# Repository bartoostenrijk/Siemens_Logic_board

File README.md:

# Siemens_Logic_board
Here I share the PCB files with which to replace an existing SIEMENS SIMOTION logic board, as used in the Think City car

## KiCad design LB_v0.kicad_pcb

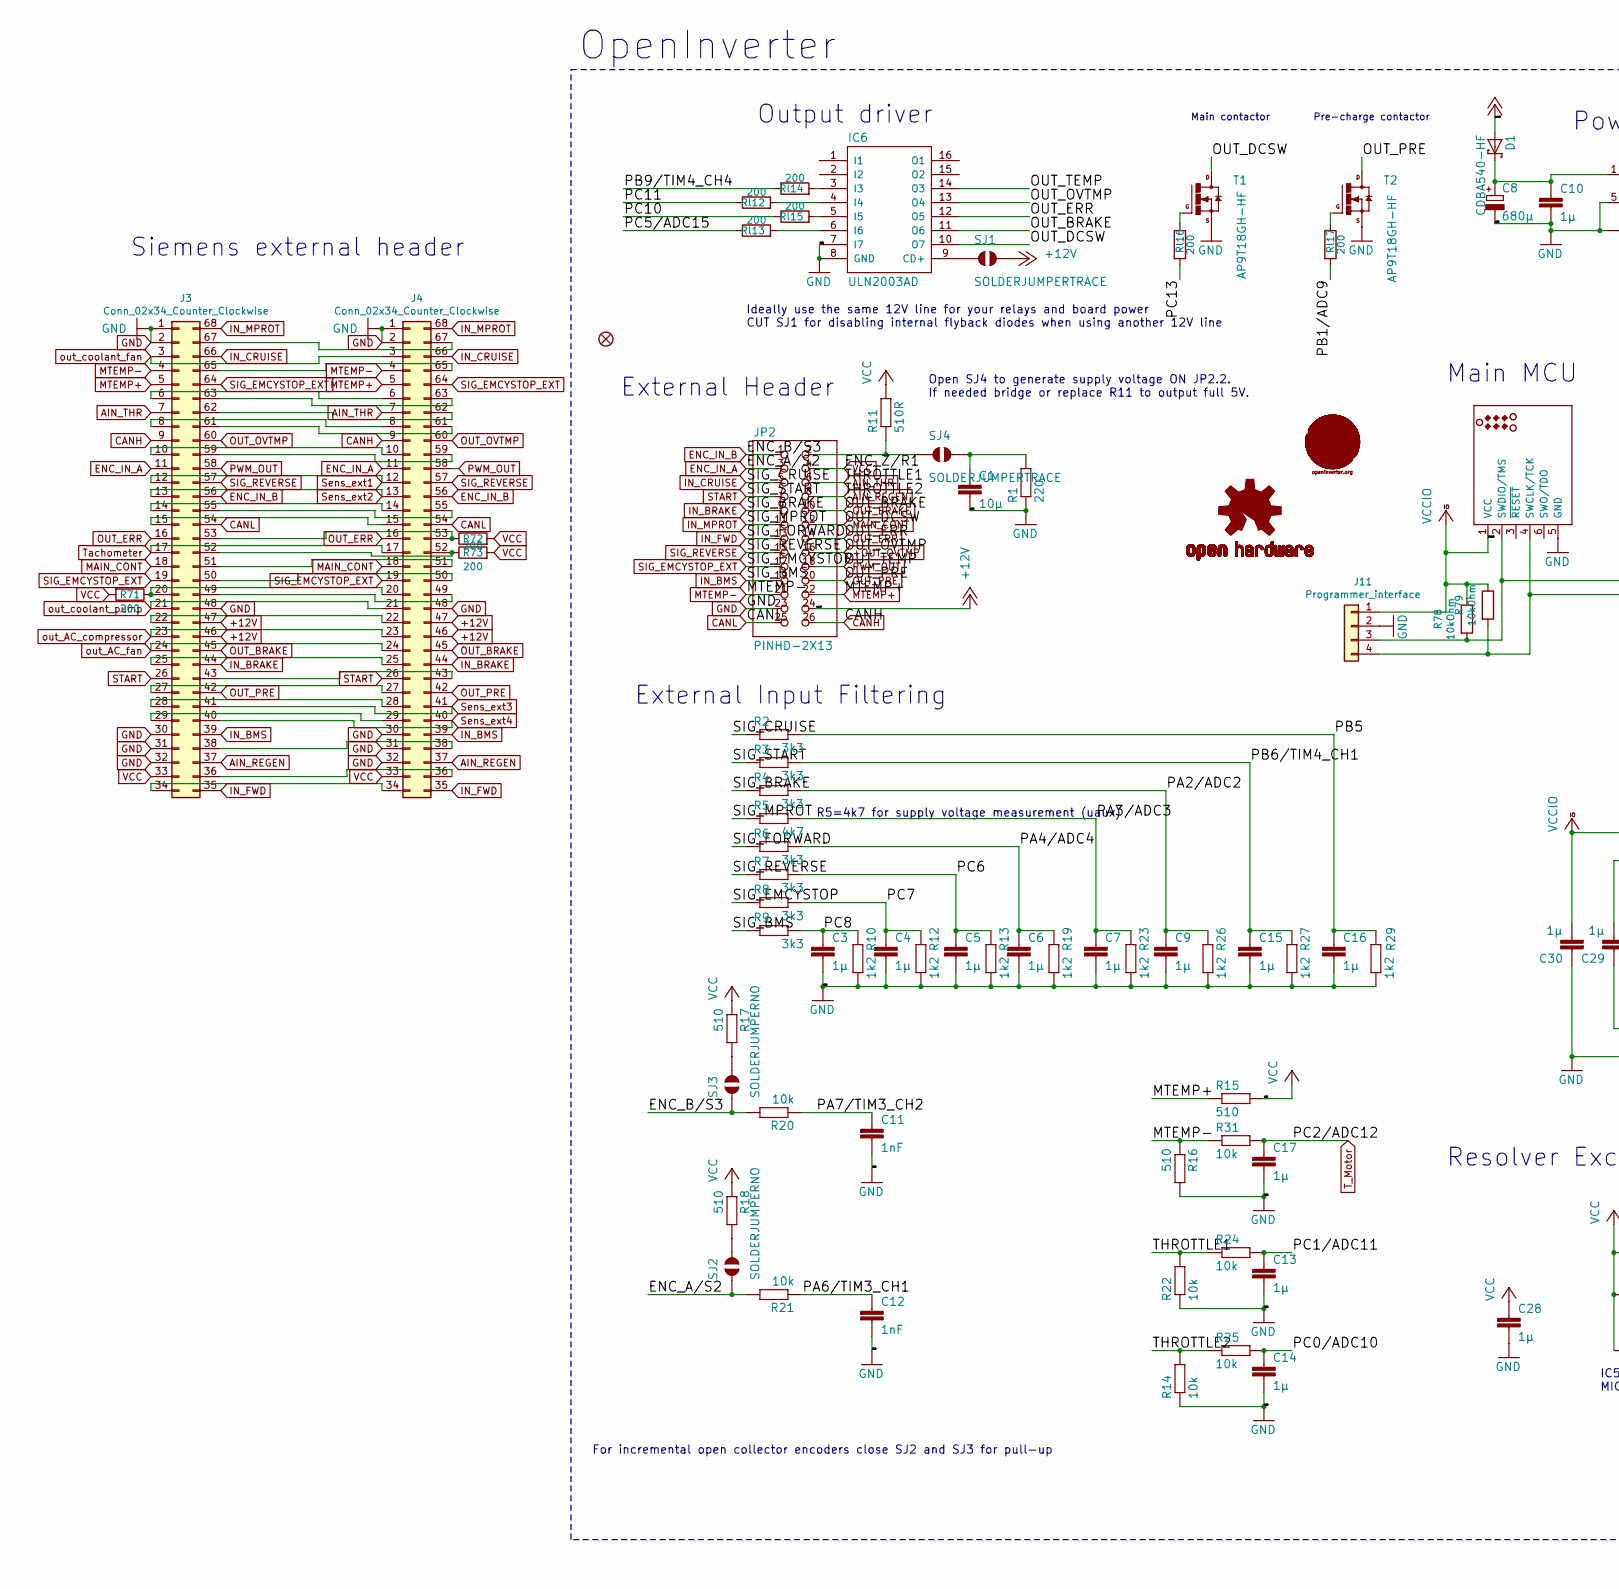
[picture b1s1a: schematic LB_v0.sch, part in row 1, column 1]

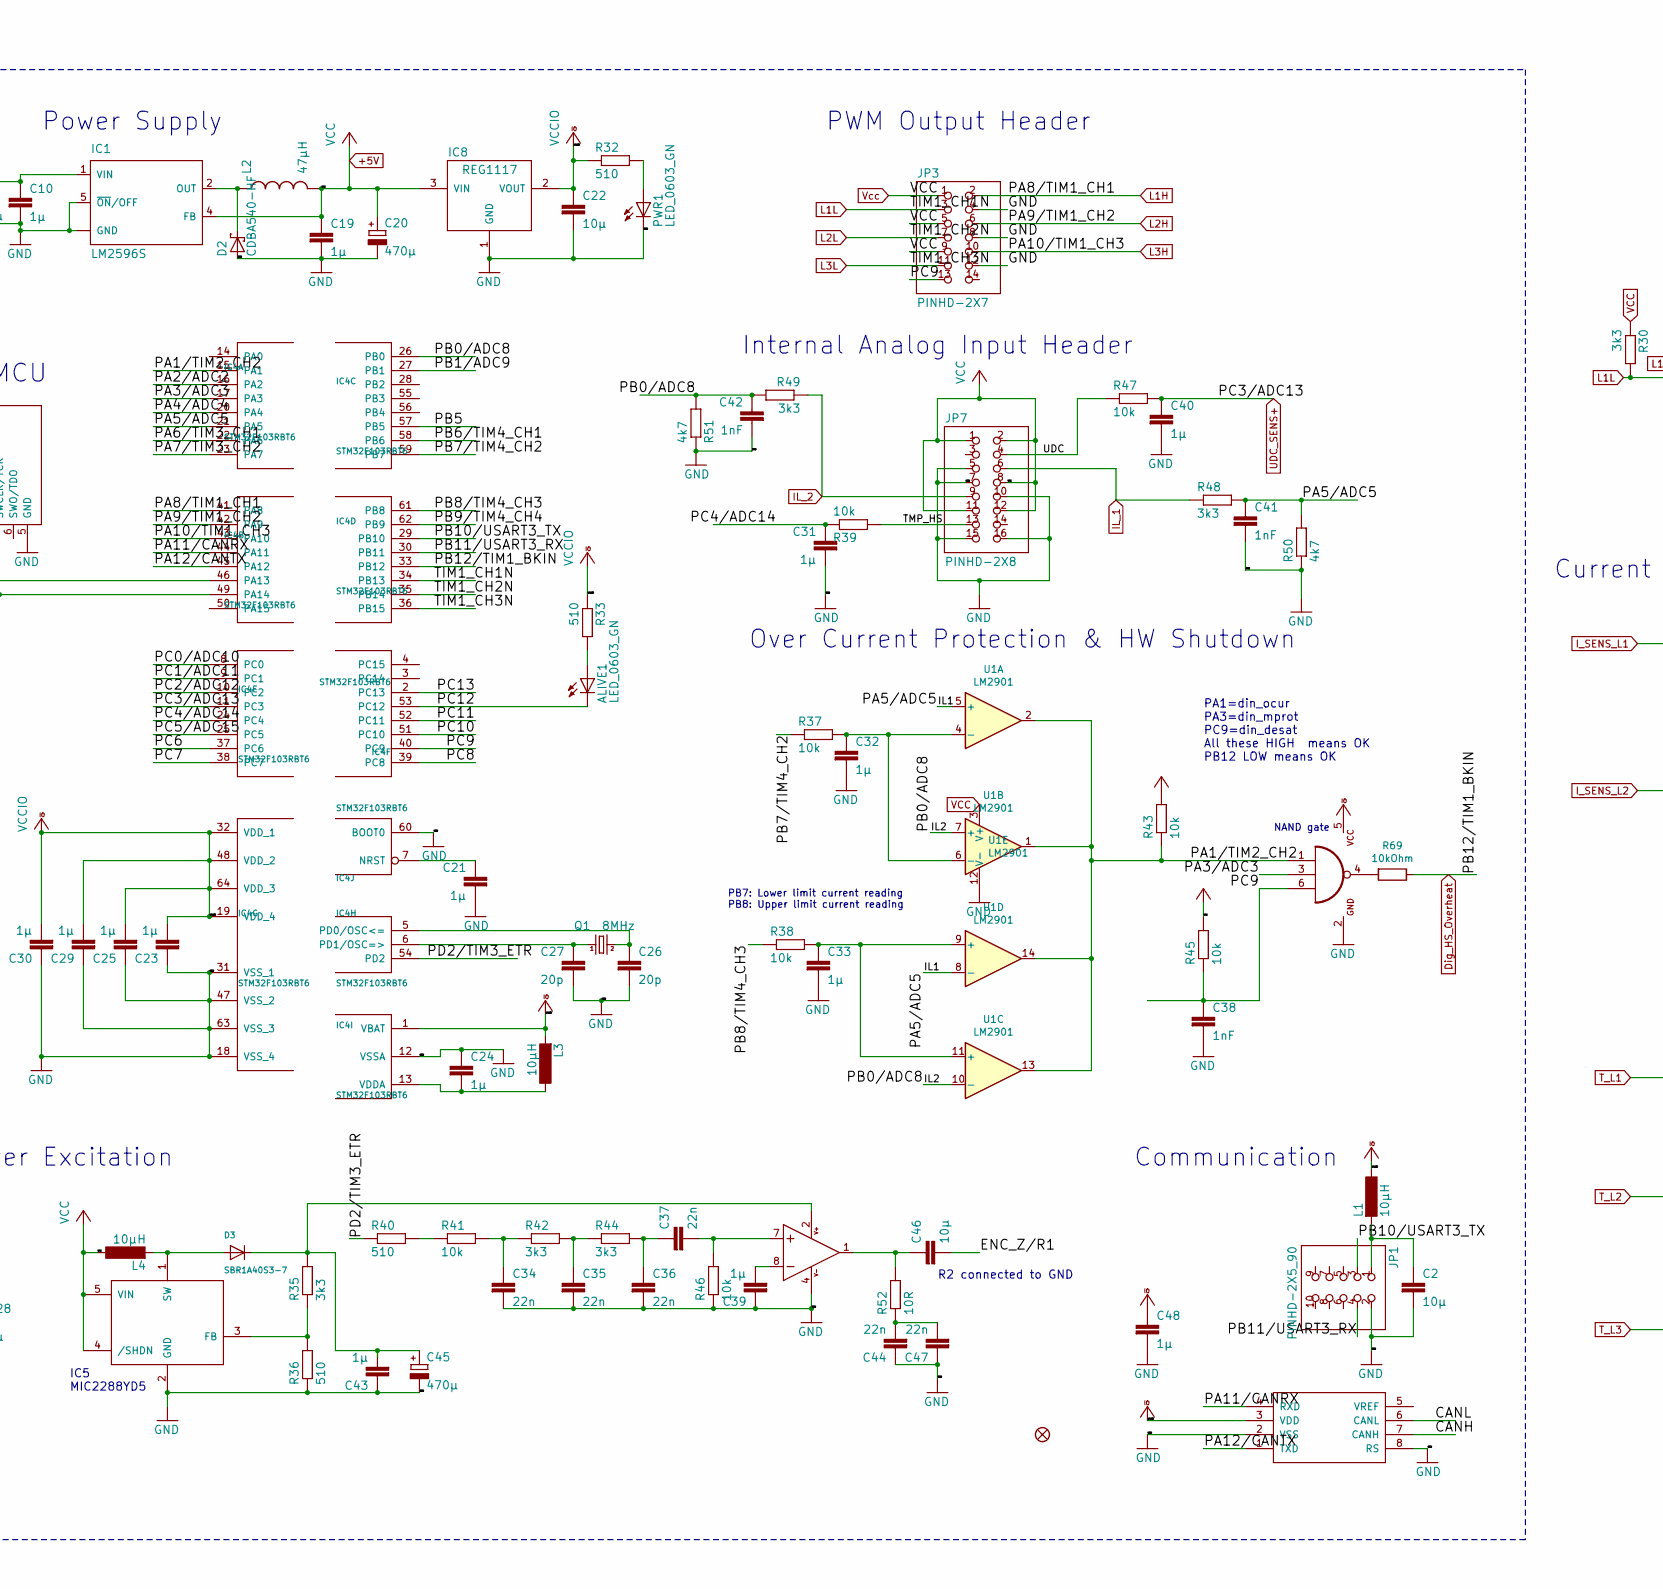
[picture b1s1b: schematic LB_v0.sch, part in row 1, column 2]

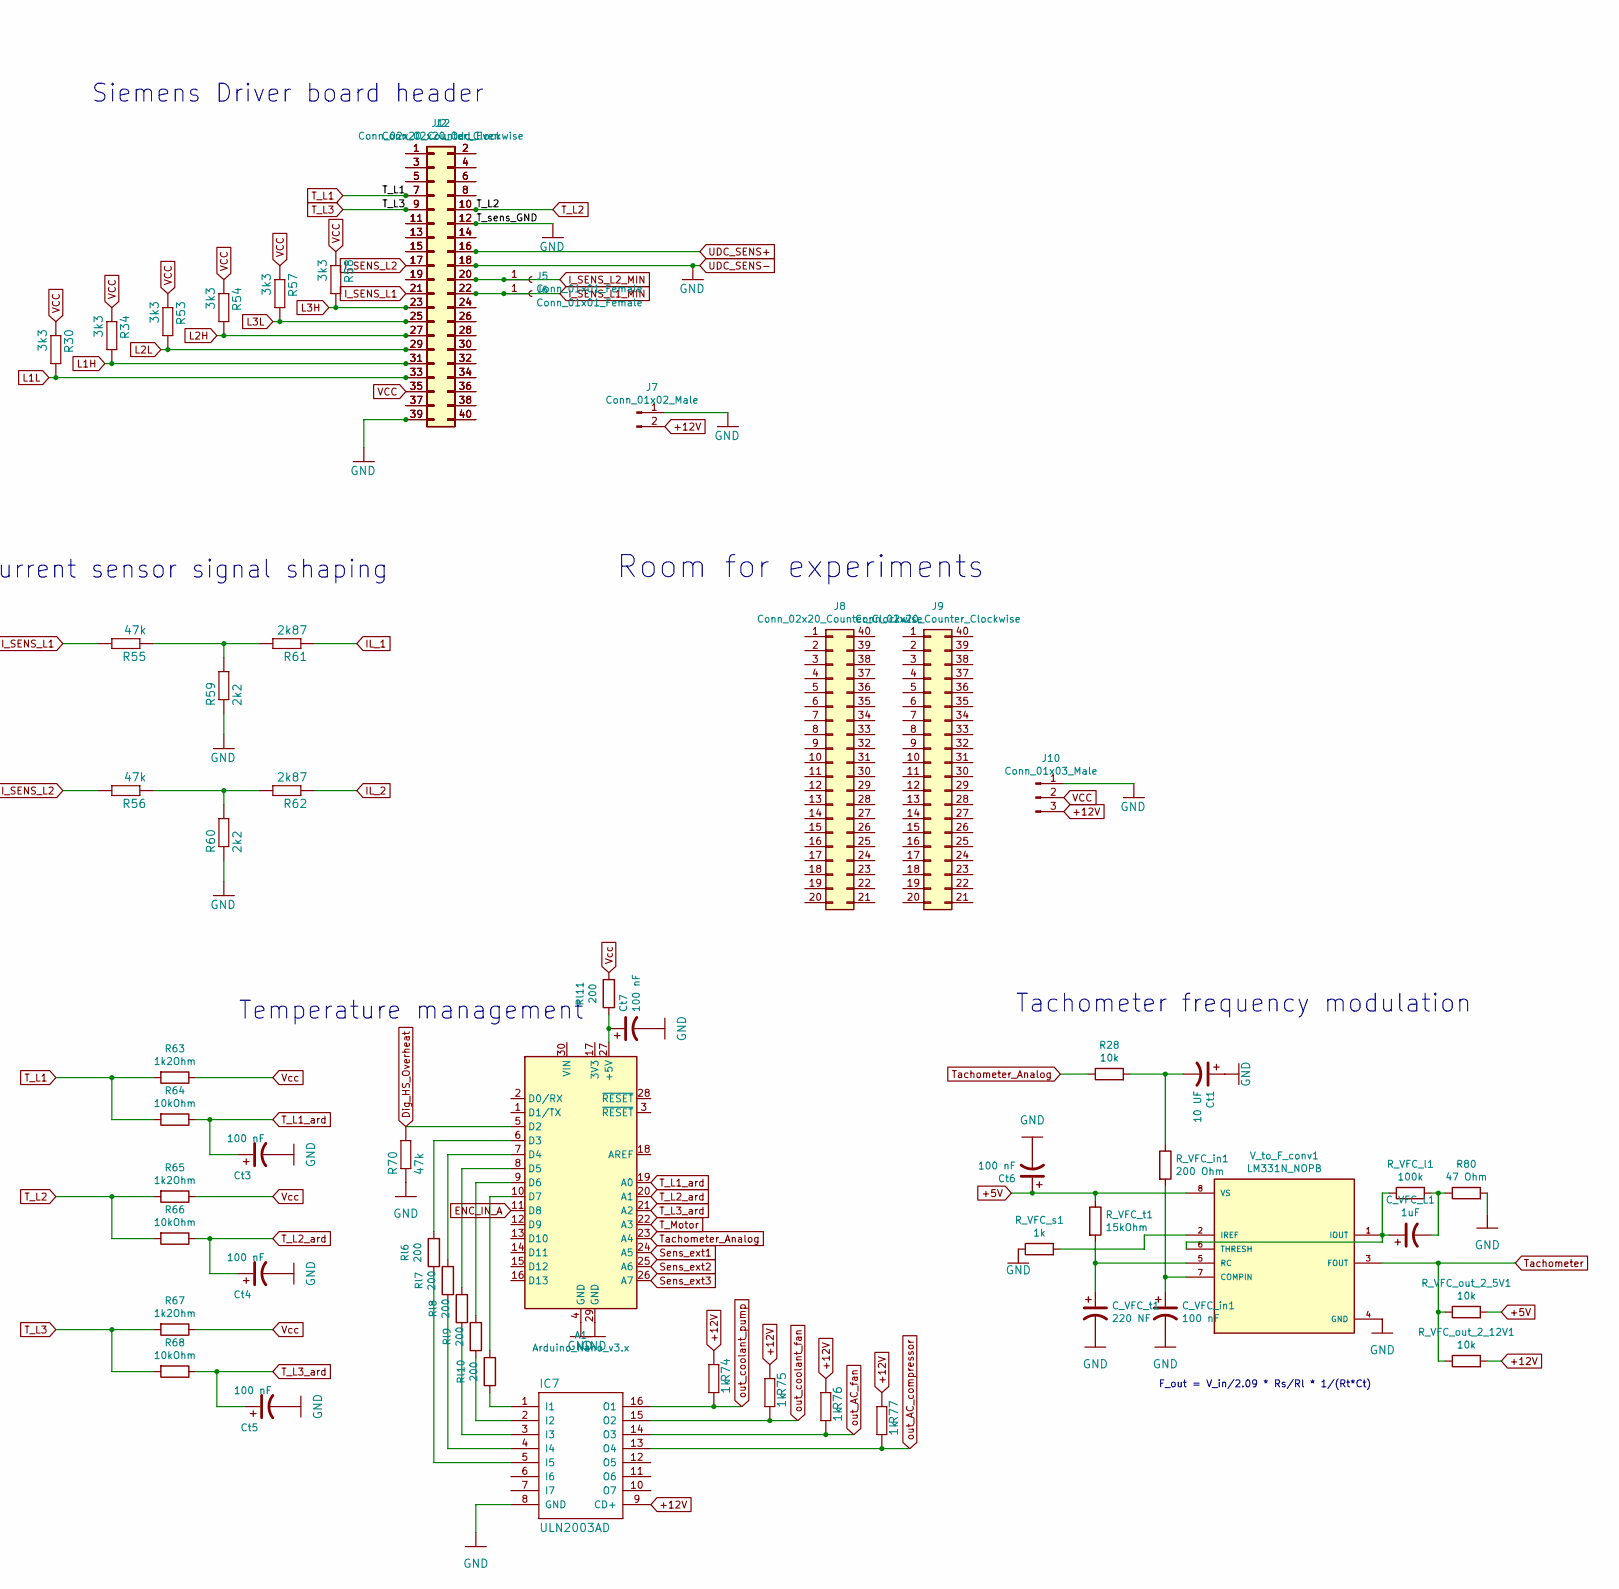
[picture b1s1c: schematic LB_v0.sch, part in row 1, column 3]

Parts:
A1: Arduino_Nano_v3.x; Arduino_Nano
ALIVE1: LED_0603_GN; SML0805; LCSC C84256
C1, C2, C22, C46: 10µ; C0805; LCSC C15850
C3, C4, C5, C6, C7, C9, C10, C13, C14, C15, C16, C17, C19, C21, C23, C24, C25, C28, C29, C30, C31, C32, C33, C39, C40, C43, C48: 1µ; C0603; LCSC C28323
C8: 680µ; UD-10X10_NICHICON; LCSC C249931
C11, C12, C38, C41, C42: 1nF; C0603; LCSC C46653
C20: 470µ; UD-6,3X7,7_NICHICON; LCSC C134738
C26, C27: 20p; C0603; LCSC C1804
C34, C35, C36, C37, C44, C47: 22n; C0603; LCSC C21122
C45: 470µ; UD-6,3X7,7_NICHICON; LCSC C134823
C_VFC_L1: 1uF; C_0805_2012Metric; LCSC C28323
C_VFC_in1: 100 nF; C_0603_1608Metric; LCSC C14663
C_VFC_t1: 220 NF; C_0603_1608Metric; LCSC C21120
Ct1: 10 UF; C_0805_2012Metric; LCSC C15850
Ct3, Ct4, Ct5, Ct6, Ct7: 100 nF; C_0603_1608Metric; LCSC C14663
D1, D2: CDBA540-HF; SMB; LCSC C22452
D3: SBR1A40S3-7; SOD-323F; LCSC C2128
FID1, FID2: FIDUCIAL1X2.5; FIDUCIAL-1X2.5
IC1: LM2596S; TO263-5; LCSC C10002
IC2: TDA2822D; SO08; LCSC C73296
IC3: SN65HVD230DR; SOP-8_3.9x4.9mm_P1.27mm; LCSC C258149
IC4: STM32F103RBT6; TQFP64; LCSC C46034
IC5: MIC2288YD5; SOT23-5L; LCSC C7722
IC6, IC7: ULN2003AD; SO16; LCSC C7512
IC8: REG1117; SOT223; LCSC C347229
IC9: NC7SZ10P6X; SC70-6; LCSC C258149
J1: TC2030_SWD-MCP; TC2030-MCP
J2: Conn_02x20_Odd_Even; PinHeader_2x20_P1.27mm_Vertical_SMD
J3, J4: Conn_02x34_Counter_Clockwise; TE_connector_Siemens
J5, J6: Conn_01x01_Female; SolderWirePad_1x01_Drill1mm
J7: Conn_01x02_Male; SolderWirePad_1x02_P7.62mm_Drill2mm
J8, J9, J12: Conn_02x20_Counter_Clockwise; PinHeader_2x20_P2.54mm_Vertical
J10: Conn_01x03_Male; PinHeader_1x03_P2.54mm_Vertical
J11: Programmer_interface; PinHeader_1x04_P2.54mm_Vertical
JP1: PINHD-2X5_90; 2X05_90
JP2: PINHD-2X13; 2X13
JP3: PINHD-2X7; 2X07
JP7: PINHD-2X8; 2X08
L1, L3: 10µH; L2012C; LCSC C1046
L2: 47µH; CDRH125; LCSC C167265
L4: 10µH; L2825P; LCSC C86069
LOGO1: OSHW-LOGOM; OSHW-LOGO-M
PWR1: LED_0603_GN; SML0805; LCSC C84256
Q1: 8MHz; CRYSTAL-TXC-7A; LCSC C115962
R1: 220; R0603; LCSC C22962
R2, R3, R4, R6, R7, R8, R9, R35, R42, R44, R48, R49: 3k3; R0603; LCSC C26010
R5, R50, R51: 4k7; R0603; LCSC C17673
R10, R12, R13, R19, R23, R26, R27, R29: 1k2; R0603; LCSC C22765
R11: 510R; R0603; LCSC C23193
R14, R20, R21, R22, R24, R25, R31, R37, R38, R39, R41, R43, R46, R47: 10k; R0603; LCSC C17414
R15, R16, R32, R33, R36, R40: 510; R0603; LCSC C23193
R17, R18: 510; R0603
R28: 10k; R_Axial_DIN0207_L6.3mm_D2.5mm_P7.62mm_Horizontal
R30, R34, R53, R54, R57, R58: 3k3; R0603; LCSC C25890
R45: 10k; R_1206_3216Metric; LCSC C17902
R52: 10R; R0603; LCSC C22859
R55, R56, R70: 47k; R_0805_2012Metric; LCSC C17713
R59, R60: 2k2; R_0805_2012Metric; LCSC C17520
R61, R62: 2k87; R_0805_2012Metric; LCSC C17533
R63, R65, R67: 1k2Ohm; R_0603_1608Metric; LCSC C22765
R64, R66, R68, R69, R78, R79: 10kOhm; R_1206_3216Metric; LCSC C17902
R71, R72, R73: 200; R_0402_1005Metric; LCSC C25087
R74, R75, R76, R77: 1k; R_0805_2012Metric; LCSC C17513
R80: 47 Ohm; R_0805_2012Metric; LCSC C17714
R_VFC_in1: 200 Ohm; R_0402_1005Metric; LCSC C25087
R_VFC_l1: 100k; R_Axial_DIN0204_L3.6mm_D1.6mm_P5.08mm_Horizontal
R_VFC_out_2_5V1, R_VFC_out_2_12V1: 10k; R_Axial_DIN0207_L6.3mm_D2.5mm_P7.62mm_Horizontal
R_VFC_s1: 1k; R_0603_1608Metric; LCSC C21190
R_VFC_t1: 15kOhm; R_0402_1005Metric; LCSC C25756
Rl6, Rl7, Rl8, Rl9, Rl10, Rl11, Rl12, Rl13, Rl14, Rl15, Rl16, Rl17: 200; R_0402_1005Metric; LCSC C25087
SJ1, SJ4: SOLDERJUMPERTRACE; SJ_2S-TRACE
SJ2, SJ3: SOLDERJUMPERNO; SJ_2S-NO
T1, T2: AP9T18GH-HF; D-PAK_TO252AA; LCSC C124546
U1: LM2901; SOIC-14_3.9x8.7mm_P1.27mm; LCSC C14296
U$1: OI-LOGO; OI_LOGO
V_to_F_conv1: LM331N_NOPB; DIP-8_W7.62mm; PARTREV 4040082/E 04/2010

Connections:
+5V: C19.1, C20.+, C28.1, C46.2, Ct6.1, IC1.4 (FB), IC5.4 (/SHDN), IC5.5 (VIN), IC8.3 (VIN), J2.35, J3.33, J4.33, J10.2, J12.35, JP2.4, JP3.1, JP3.5, JP3.9, JP7.1, JP7.2, JP7.8, JP7.11, JP7.12, L2.2, L4.1, R11.2, R15.2, R17.1, R18.1, R30.1, R34.1, R43.2, R45.2, R53.1, R54.1, R57.1, R58.1, R63.1, R65.1, R67.1, R71.2, R72.2, R73.2, R_VFC_out_2_5V1.2, R_VFC_t1.1, Rl11.2, U1.3 (V+), V_to_F_conv1.8 (VS)
+12V: D1.A, IC7.9 (CD+), J3.46, J3.47, J4.46, J4.47, J7.2, J10.3, JP2.24, R74.1, R75.1, R76.1, R77.1, R_VFC_out_2_12V1.2, SJ1.2
+OUT_OVTMP: IC6.13 (O4), J3.60, J4.60, JP2.16
/IL1: C41.1, IC4.21 (PA5), R48.2, R50.2, U1.5 (+), U1.8 (-)
/IL2: C42.1, IC4.26 (PB0), R49.2, R51.2, U1.7 (+), U1.10 (-)
/PA1/TIM2_CH2: IC4.15 (PA1), IC9.1 (I0), R43.1, U1.1, U1.2, U1.13, U1.14
/PA2/ADC2: C9.1, IC4.16 (PA2), R4.2, R26.2
/PA3/ADC3: C7.1, IC4.17 (PA3), IC9.3 (I1), R5.2, R23.2
/PA4/ADC4: C6.1, IC4.20 (PA4), R6.2, R19.2
/PA6/TIM3_CH1: C12.1, IC4.22 (PA6), R21.1
/PA7/TIM3_CH2: C11.1, IC4.23 (PA7), R20.1
/PA11/CANRX: IC3.4 (RXD), IC4.44 (PA11)
/PA12/CANTX: IC3.1 (TXD), IC4.45 (PA12)
/PB1/ADC9: IC4.27 (PB1), Rl17.2
/PB5: C16.1, IC4.57 (PB5), R2.2, R29.2
/PB6/TIM4_CH1: C15.1, IC4.58 (PB6), R3.2, R27.2
/PB7/TIM4_CH2: IC4.59 (PB7), R37.1
/PB8/TIM4_CH3: IC4.61 (PB8), R38.1
/PB9/TIM4_CH4: IC4.62 (PB9), Rl14.1
/PB10/USART3_TX: IC4.29 (PB10), JP1.3
/PB11/USART3_RX: IC4.30 (PB11), JP1.4
/PC0/ADC10: C14.1, IC4.8 (PC0), R25.2
/PC1/ADC11: C13.1, IC4.9 (PC1), R24.2
/PC4/ADC14: C31.1, IC4.24 (PC4), R39.1
/PC5/ADC15: IC4.25 (PC5), Rl13.1
/PC6: C5.1, IC4.37 (PC6), R7.2, R13.2
/PC7: C4.1, IC4.38 (PC7), R8.2, R12.2
/PC8: C3.1, IC4.39 (PC8), R9.2, R10.2
/PC9: C38.1, IC4.40 (PC9), IC9.6 (I2), JP3.13, R45.1
/PC10: IC4.51 (PC10), Rl15.1
/PC11: IC4.52 (PC11), Rl12.1
/PC12: ALIVE1.C, IC4.53 (PC12)
/PC13: IC4.2 (PC13), Rl16.2
/PD2/TIM3_ETR: IC4.54 (PD2), R40.1
/TMP_HS: JP7.13, R39.2
/UDC: JP7.4, R47.1
AIN_REGEN: J3.37, J4.37, JP2.8, R14.2, R25.1
AIN_THR: J3.7, J4.7, JP2.6, R22.2, R24.1
CANH: IC3.7 (CANH), J3.9, J4.9, JP2.26
CANL: IC3.6 (CANL), J3.54, J4.54, JP2.25
Dig_HS_Overheat: A1.5 (D2), IC4.33 (PB12), R69.1, R70.2
ENC_IN_A: A1.11 (D8), J3.11, J4.11, JP2.3, R21.2, SJ2.1
ENC_IN_B: J3.56, J4.56, JP2.1, R20.2, SJ3.1
GND: A1.4 (GND), A1.29 (GND), C1.2, C2.2, C3.2, C4.2, C5.2, C6.2, C7.2, C8.-, C9.2, C10.2, C11.2, C12.2, C13.2, C14.2, C15.2, C16.2, C17.2, C19.2, C20.-, C21.2, C22.2, C23.1, C24.1, C25.1, C26.2, C27.2, C28.2, C29.1, C30.1, C31.2, C32.2, C33.2, C34.2, C35.2, C36.2, C38.2, C39.1, C40.2, C41.2, C42.2, C43.1, C44.1, C45.-, C47.1, C48.2, C_VFC_in1.2, C_VFC_t1.2, Ct1.1, Ct3.2, Ct4.2, Ct5.2, Ct6.2, Ct7.2, D2.A, IC1.3 (GND), IC1.5 (~ON~/OFF), IC1.6 (GND), IC2.4 (V-), IC3.2 (VSS), IC3.8 (RS), IC4.12 (VSSA), IC4.18 (VSS_4), IC4.31 (VSS_1), IC4.47 (VSS_2), IC4.60 (BOOT0), IC4.63 (VSS_3), IC5.2 (GND), IC6.7 (I7), IC6.8 (GND), IC7.8 (GND), IC8.1 (GND), IC9.2 (GND), J1.5 (GND), J2.12, J2.18, J2.39, J3.1, J3.2, J3.30, J3.31, J3.32, J3.48, J4.1, J4.2, J4.30, J4.31, J4.32, J4.48, J7.1, J10.1, J11.2, J12.12, J12.18, J12.39, JP1.2, JP2.23, JP3.4, JP3.8, JP3.12, JP7.5, JP7.7, JP7.10, JP7.15, JP7.16, PWR1.C, R1.1, R10.1, R12.1, R13.1, R14.1, R16.2, R19.1, R22.1, R23.1, R26.1, R27.1, R29.1, R36.1, R46.1, R50.1, R51.1, R59.1, R60.1, R70.1, R80.2, R_VFC_s1.1, T1.3 (S), T2.3 (S), U1.12 (V-), V_to_F_conv1.4 (GND)
IL_1: JP7.6, R48.1, R61.1
IL_2: JP7.9, R49.1, R62.1
IN_BMS: J3.39, J4.39, JP2.19, R9.1
IN_BRAKE: J3.44, J4.44, JP2.9, R4.1
IN_CRUISE: J3.66, J4.66, JP2.5, R2.1
IN_FWD: J3.35, J4.35, JP2.13, R6.1
IN_MPROT: J3.68, J4.68, JP2.11, R5.1
I_SENS_L1: J2.21, J12.21, R55.2
I_SENS_L1_MIN: J2.22, J6.1, J12.22
I_SENS_L2: J2.17, J12.17, R56.2
I_SENS_L2_MIN: J2.20, J5.1, J12.20
L1H: IC4.41 (PA8), J2.31, J12.31, JP3.2, R34.2
L1L: IC4.34 (PB13), J2.33, J12.33, JP3.3, R30.2
L2H: IC4.42 (PA9), J2.27, J12.27, JP3.6, R54.2
L2L: IC4.35 (PB14), J2.29, J12.29, JP3.7, R53.2
L3H: IC4.43 (PA10), J2.23, J12.23, JP3.10, R58.2
L3L: IC4.36 (PB15), J2.25, J12.25, JP3.11, R57.2
MAIN_CONT: IC6.10 (O7), J3.18, J4.18, JP2.12, T1.4 (D)
MTEMP+: J3.5, J4.5, JP2.22, R15.1
MTEMP-: J3.4, J4.4, JP2.21, R16.1, R31.1
unnamed: A1.6 (D3), Rl6.2
unnamed: A1.7 (D4), Rl7.2
unnamed: A1.8 (D5), Rl8.2
unnamed: A1.9 (D6), Rl9.2
unnamed: A1.10 (D7), Rl10.2
unnamed: A1.27 (+5V), Ct7.1, Rl11.1
unnamed: ALIVE1.A, R33.2
unnamed: C1.1, R1.2, SJ4.2
unnamed: C2.1, JP1.1, L1.2
unnamed: C8.+, C10.1, D1.C, IC1.1 (VIN)
unnamed: C21.1, IC4.7 (NRST)
unnamed: C24.2, IC4.13 (VDDA), L3.1
unnamed: C26.1, IC4.5 (PD0/OSC<=), Q1.P$2 (2)
unnamed: C27.1, IC4.6 (PD1/OSC=>), Q1.P$1 (1)
unnamed: C32.1, R37.2, U1.4 (-), U1.6 (-)
unnamed: C33.1, R38.2, U1.9 (+), U1.11 (+)
unnamed: C34.1, R41.2, R42.1
unnamed: C35.1, R42.2, R44.1
unnamed: C36.1, C37.1, R44.2
unnamed: C37.2, IC2.7 (+IN), R46.2
unnamed: C39.2, IC2.8 (-IN)
unnamed: C43.2, C45.+, D3.C, IC2.2 (V+), R35.2
unnamed: C44.2, C47.2, R52.1
unnamed: C46.1, IC2.1 (OUT), R52.2
unnamed: C_VFC_L1.1, R_VFC_l1.1, V_to_F_conv1.1 (IOUT), V_to_F_conv1.6 (THRESH)
unnamed: C_VFC_L1.2, R80.1, R_VFC_l1.2
unnamed: C_VFC_in1.1, R_VFC_in1.2, V_to_F_conv1.7 (COMPIN)
unnamed: C_VFC_t1.1, R_VFC_t1.2, V_to_F_conv1.5 (RC)
unnamed: Ct1.2, R28.2, R_VFC_in1.1
unnamed: D2.C, IC1.2 (OUT), L2.1
unnamed: D3.A, IC5.1 (SW), L4.2
unnamed: IC4.46 (PA13), J1.2 (SWDIO/TMS), J11.3, R78.2
unnamed: IC4.49 (PA14), J1.4 (SWCLK/TCK), J11.4, R79.2
unnamed: IC5.3 (FB), R35.1, R36.2
unnamed: IC6.3 (I3), Rl14.2
unnamed: IC6.4 (I4), Rl12.2
unnamed: IC6.5 (I5), Rl15.2
unnamed: IC6.6 (I6), Rl13.2
unnamed: IC6.9 (CD+), SJ1.1
unnamed: IC7.1 (I1), Rl10.1
unnamed: IC7.2 (I2), Rl9.1
unnamed: IC7.3 (I3), Rl8.1
unnamed: IC7.4 (I4), Rl7.1
unnamed: IC7.5 (I5), Rl6.1
unnamed: IC9.4 (O), R69.2
unnamed: J3.6, J4.6
unnamed: J3.8, J4.8
unnamed: J3.10, J4.10
unnamed: J3.14, J4.14
unnamed: J3.15, J4.15
unnamed: J3.20, J4.20, R71.1
unnamed: J3.22, J4.22
unnamed: J3.25, J4.25
unnamed: J3.27, J4.27
unnamed: J3.28, J4.28
unnamed: J3.29, J4.29
unnamed: J3.34, J4.34
unnamed: J3.36, J4.36
unnamed: J3.38, J4.38
unnamed: J3.43, J4.43
unnamed: J3.49, J4.49
unnamed: J3.50, J4.50
unnamed: J3.51, J4.51
unnamed: J3.52, J4.52, R73.1
unnamed: J3.53, J4.53, R72.1
unnamed: J3.55, J4.55
unnamed: J3.59, J4.59
unnamed: J3.61, J4.61
unnamed: J3.62, J4.62
unnamed: J3.63, J4.63
unnamed: J3.65, J4.65
unnamed: J3.67, J4.67
unnamed: J2.1, J12.1
unnamed: J2.2, J12.2
unnamed: J2.3, J12.3
unnamed: J2.4, J12.4
unnamed: J2.5, J12.5
unnamed: J2.6, J12.6
unnamed: J2.8, J12.8
unnamed: J2.11, J12.11
unnamed: J2.13, J12.13
unnamed: J2.14, J12.14
unnamed: J2.15, J12.15
unnamed: J2.19, J12.19
unnamed: J2.24, J12.24
unnamed: J2.26, J12.26
unnamed: J2.28, J12.28
unnamed: J2.30, J12.30
unnamed: J2.32, J12.32
unnamed: J2.34, J12.34
unnamed: J2.36, J12.36
unnamed: J2.37, J12.37
unnamed: J2.38, J12.38
unnamed: J2.40, J12.40
unnamed: JP2.2, R11.1, SJ4.1
unnamed: PWR1.A, R32.2
unnamed: R17.2, SJ3.2
unnamed: R18.2, SJ2.2
unnamed: R40.2, R41.1
unnamed: R55.1, R59.2, R61.2
unnamed: R56.1, R60.2, R62.2
unnamed: R_VFC_s1.2, V_to_F_conv1.2 (IREF)
unnamed: Rl16.1, T1.1 (G)
unnamed: Rl17.1, T2.1 (G)
OUT_BRAKE: IC6.11 (O6), J3.45, J4.45, JP2.10
OUT_ERR: IC6.12 (O5), J3.16, J4.16, JP2.14
OUT_PRE: J3.42, J4.42, JP2.20, T2.4 (D)
PWM_OUT: IC6.14 (O3), J3.58, J4.58, JP2.18
SIG_EMCYSTOP_EXT: J3.19, J3.64, J4.19, J4.64, JP2.17, R8.1
SIG_REVERSE: J3.57, J4.57, JP2.15, R7.1
START: J3.26, J4.26, JP2.7, R3.1
Sens_ext1: A1.24 (A5), J3.12, J4.12
Sens_ext2: A1.25 (A6), J3.13, J4.13
Sens_ext3: A1.26 (A7), J3.41, J4.41
Sens_ext4: J3.40, J4.40
T_L1: J2.7, J12.7, R63.2, R64.2
T_L1_ard: A1.19 (A0), Ct3.1, R64.1
T_L2: J2.10, J12.10, R65.2, R66.2
T_L2_ard: A1.20 (A1), Ct4.1, R66.1
T_L3: J2.9, J12.9, R67.2, R68.2
T_L3_ard: A1.21 (A2), Ct5.1, R68.1
T_Motor: A1.22 (A3), C17.1, IC4.10 (PC2), R31.2
Tachometer: J3.17, J4.17, R_VFC_out_2_5V1.1, R_VFC_out_2_12V1.1, V_to_F_conv1.3 (FOUT)
Tachometer_Analog: A1.23 (A4), R28.1
UDC_SENS+: C40.1, IC4.11 (PC3), J2.16, J12.16, R47.2
VCCIO: C22.1, C23.2, C25.2, C29.2, C30.2, C48.1, IC3.3 (VDD), IC4.1 (VBAT), IC4.19 (VDD_4), IC4.32 (VDD_1), IC4.48 (VDD_2), IC4.64 (VDD_3), IC8.2 (VOUT), IC9.5 (VCC), J1.1 (VCC), J11.1, L1.1, L3.2, R32.1, R33.1, R78.1, R79.1
out_AC_compressor: IC7.13 (O4), J3.23, J4.23, R77.2
out_AC_fan: IC7.14 (O3), J3.24, J4.24, R76.2
out_coolant_fan: IC7.15 (O2), J3.3, J4.3, R75.2
out_coolant_pump: IC7.16 (O1), J3.21, J4.21, R74.2

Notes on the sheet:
Output driver
Resolver Excitation
For incremental open collector encoders close SJ2 and SJ3 for pull-up
R2 connected to GND
Open SJ4 to generate supply voltage ON JP2.2. If needed bridge or replace R11 to output full 5V.
External Input Filtering
Ideally use the same 12V line for your relays and board power CUT SJ1 for disabling internal flyback diodes when using another 12V line
External Header
Communication
Power Supply
PWM Output Header
Internal Analog Input Header
Main MCU
PA1=din_ocur PA3=din_mprot PC9=din_desat All these HIGH means OK PB12 LOW means OK
R5=4k7 for supply voltage measurement (uaux)
IC5 MIC2288YD5
Siemens Driver board header
Siemens external header
Current sensor signal shaping
Over Current Protection & HW Shutdown
Temperature management
NAND gate
PB7: Lower limit current reading PB8: Upper limit current reading
Main contactor
Pre-charge contactor
Room for experiments
OpenInverter
F_out = V_in/2.09 * Rs/Rl * 1/(Rt*Ct)
Tachometer frequency modulation

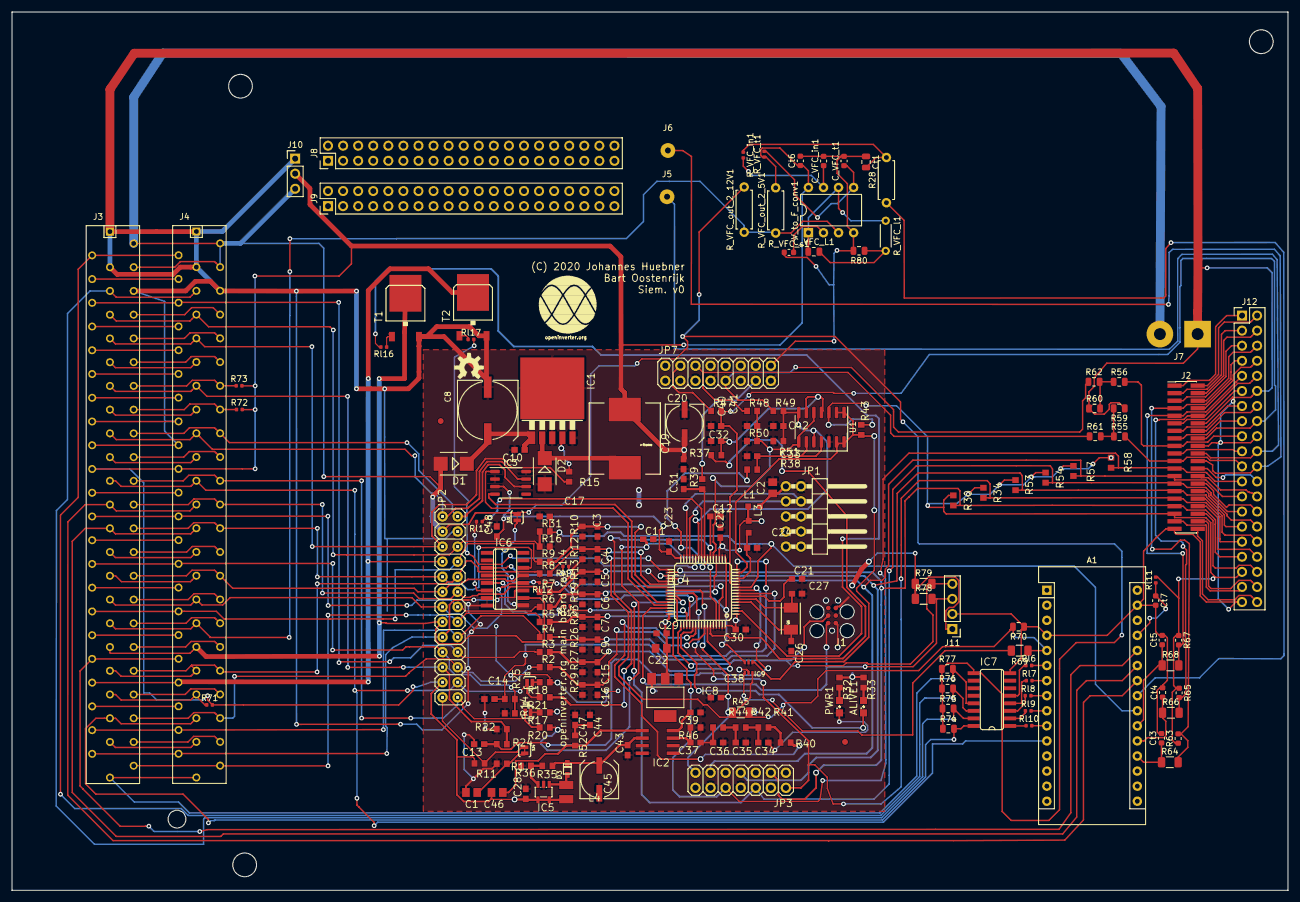
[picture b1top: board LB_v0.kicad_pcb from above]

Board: 2 copper layers, 215.0 x 148.0 mm, 202 parts (0 on the bottom side), 194 nets.

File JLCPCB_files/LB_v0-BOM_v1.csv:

Reference, Quantity, Value, Footprint, LCSC
C12 C41 C42 C11 C38 ,5,1nF,C0603,C46653
C20 C45 ,2,470µ,"UD-6,3X7,7_NICHICON",C134738
C22 C1 C46 C2 ,4,10µ,C0805,C15850
C26 C27 ,2,20p,C0603,C1804
C3 C4 C5 C6 C7 C9 C15 C16 C17 C40 C33 C19 C10 C13 C14 C23 C25 C29 C30 C24 C21 C43 C28 C39 C31 C48 C32 ,27,1µ,C0603,C28323
C34 C35 C36 C37 C44 C47 ,6,22n,C0603,C21122
C8 ,1,680µ,UD-10X10_NICHICON,C249931
C_VFC_L1 ,1,1uF,Capacitor_SMD:C_0805_2012Metric,C28323
C_VFC_t1 ,1,220 NF,Capacitor_SMD:C_0603_1608Metric,C21120
Ct1 ,1,10 UF,Capacitor_SMD:C_0805_2012Metric,C15850
Ct3 Ct4 Ct5 Ct7 Ct6 C_VFC_in1 ,6,100 nF,Capacitor_SMD:C_0603_1608Metric,C14663
D2 D1 ,2,CDBA540-HF,SMB,C22452 
D3 ,1,SBR1A40S3-7,SOD-323F,C2128
IC1 ,1,LM2596S,TO263-5,C10002
IC2 ,1,TDA2822D,SO08,C73296
IC3 ,1,SN65HVD230DR,SO08,C12084
IC4 ,1,STM32F103RBT6,TQFP64,C46034
IC5 ,1,MIC2288YD5,SOT23-5L,C7722
IC6 IC7 ,2,ULN2003AD,SO16,C7512
IC8 ,1,REG1117,SOT223,C347229 
IC9 ,1,NC7SZ10P6X,SC70-6,C258149
L2 ,1,47µH,CDRH125,C167265
L3 L1 ,2,10µH,L2012C,C1046
L4 ,1,10µH,L2825P,C86069
PWR1 ALIVE1 ,2,LED_0603_GN,SML0805,C84256 
Q1 ,1,8MHz,CRYSTAL-TXC-7A,C115962
R1 ,1,220,R0603,C22962
R10 R12 R13 R19 R23 R26 R27 R29 ,8,1k2,R0603,C22765
R11 ,1,510R,R0603,C23193
R15 R16 R17 R18 R40 R32 R33 R36 ,8,510,R0603,C23193
R21 R31 R47 R38 R22 R14 R43 R24 R25 R20 R39 R41 R46 R37 ,14,10k,R0603,C17414
R45 ,1,10k,Resistor_SMD:R_1206_3216Metric,C17902
R48 R49 R2 R3 R4 R6 R7 R8 R9 R42 R44 R35 R58 R57 R54 R53 R30 R34 ,18,3k3,R0603,C26010 
R5 R50 R51 ,3,4k7,R0603,C17673
R52 ,1,10R,R0603,C22859
R55 R56 R70 ,3,47k,Resistor_SMD:R_0805_2012Metric,C17713
R59 R60 ,2,2k2,Resistor_SMD:R_0805_2012Metric,C17520
R61 R62 ,2,2k87,Resistor_SMD:R_0805_2012Metric,C17533
R63 R65 R67 ,3,1k2Ohm,Resistor_SMD:R_0603_1608Metric,C22765
R64 R66 R68 R69 R78 R79 ,6,10kOhm,Resistor_SMD:R_1206_3216Metric,C17902
R71 Rl6 Rl7 Rl8 Rl9 Rl10 Rl11 R72 R73 Rl14 Rl12 Rl15 Rl13 Rl16 Rl17 ,15,200,Resistor_SMD:R_0402_1005Metric,C25087
R74 R75 R76 R77 ,4,1k,Resistor_SMD:R_0805_2012Metric,C17513
R80 ,1,47 Ohm,Resistor_SMD:R_0805_2012Metric,C17714
R_VFC_in1 ,1,200 Ohm,Resistor_SMD:R_0402_1005Metric,C25087
R_VFC_s1 ,1,1k,Resistor_SMD:R_0603_1608Metric,C21190
R_VFC_t1 ,1,15kOhm,Resistor_SMD:R_0402_1005Metric,C25756
T1 T2 ,2,AP9T18GH-HF,D-PAK_TO252AA,C124546
U1 ,1,LM2901,Package_SO:SOIC-14_3.9x8.7mm_P1.27mm,C142961

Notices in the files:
LB_v0.kicad_pcb:
(C) 2020 Johannes Huebner
parts and their libraries:
©2009 ROFA.cz - modified and updated by Robert Darlington ‹rdarlington@gmail.com›
